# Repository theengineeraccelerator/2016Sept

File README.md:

# 2016Sept
This is for all the design documentation from the September iteration of The Engineer Accelerator. 

The folder for each student contains the work they completed during the course. They are marked with the certificate they received at the end of the course. 

- *Professional Practice* indicates they received a Certificate of Completion in Professional Practice
- *Practice and Execution* indicates they received a Certificate of Completion in Professional Practice and Project Execution
- *Independent* indicates that the project was a independent study and not part of the session

for more information see on certifcation see the [Certification](http://www.engineeraccelerator.com/program/#certification) section of [Program](http://www.engineeraccelerator.com/program/) page

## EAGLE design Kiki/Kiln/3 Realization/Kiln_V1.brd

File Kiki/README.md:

# 2016Sept Kiki
This is for all the design documentation for this course

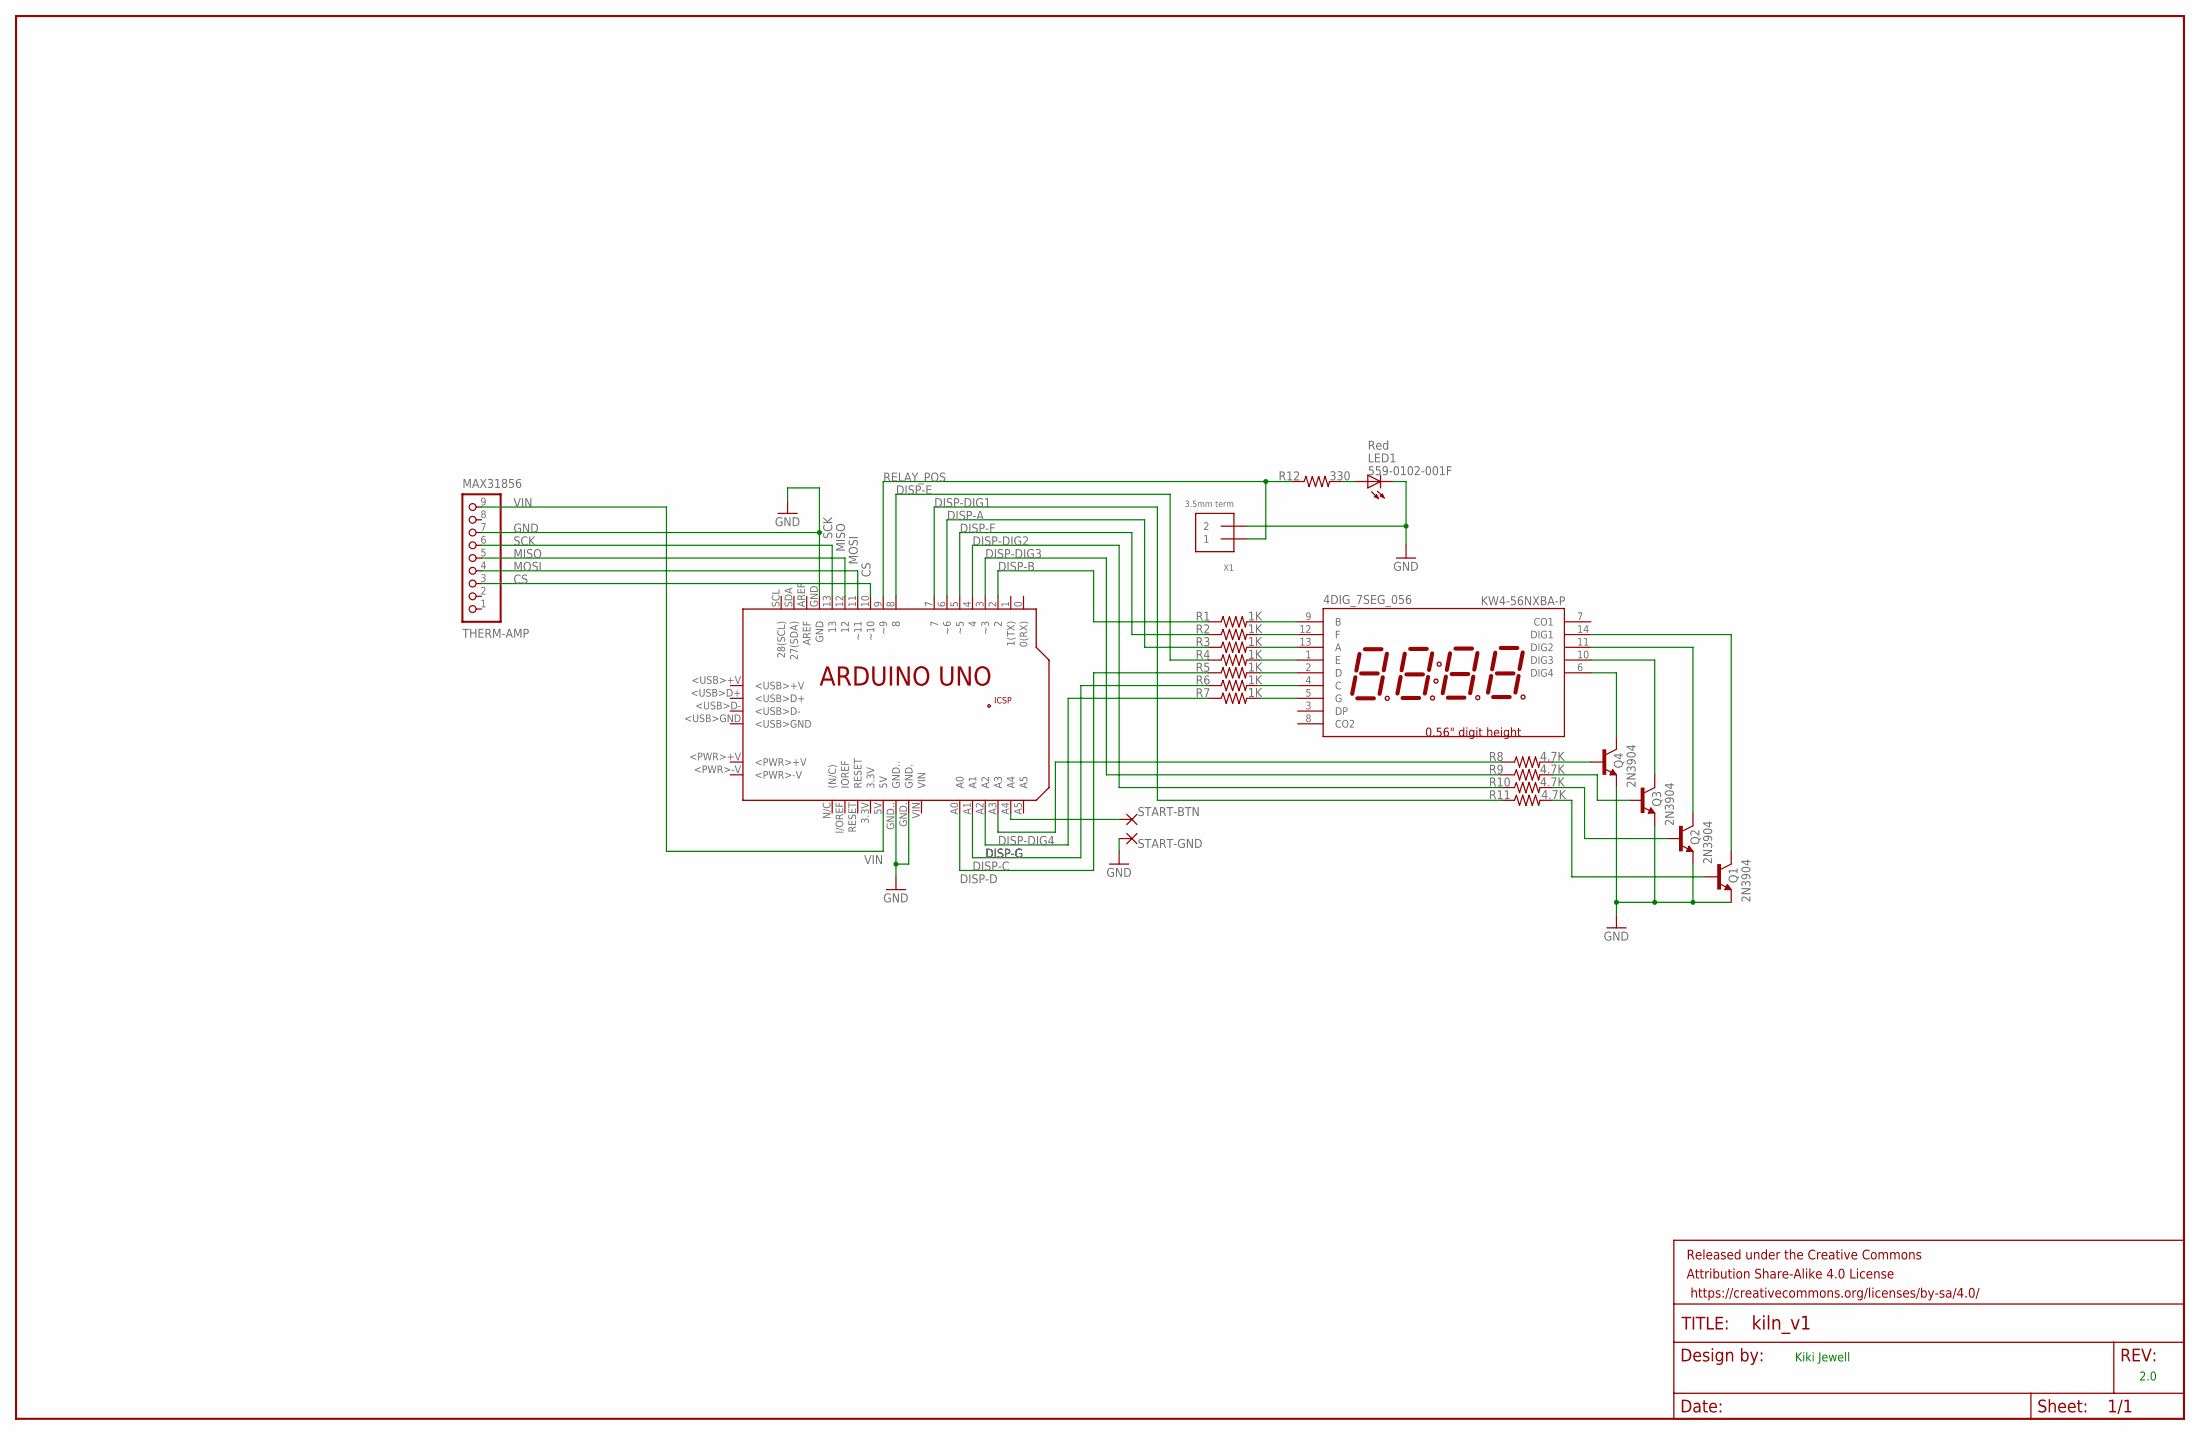
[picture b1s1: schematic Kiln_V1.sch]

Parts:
4DIG_7SEG_056: KW4-56NXBA-P; 4DIG_7SEG_056
FRAME1: FRAME-LEDGER; CREATIVE_COMMONS
LED1: 559-0102-001F; LED3MM
PCB1: ARDUINO_UNO
Q1, Q2, Q3, Q4: 2N3904; TO92
R1, R2, R3, R4, R5, R6, R7: 1K; 1206
R8, R9, R10, R11: 4.7K; 1206
R12: 330; 1206
START-BTN: WIREPAD2,54/1,1; 2,54/1,1
START-GND: WIREPAD2,54/1,1; 2,54/1,1
THERM-AMP: MAX31856; 1X09_ROUND_70
X1: 3.5mm term; TERMBLOCK_1X2-3.5MM

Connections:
A: 4DIG_7SEG_056.13 (A), R3.2
B: 4DIG_7SEG_056.9 (B), R1.2
C: 4DIG_7SEG_056.4 (C), R6.2
CS: PCB1.10 (~10), THERM-AMP.3
D: 4DIG_7SEG_056.2 (D), R5.2
DIG1: 4DIG_7SEG_056.14 (DIG1), Q1.1 (C)
DIG2: 4DIG_7SEG_056.11 (DIG2), Q2.1 (C)
DIG3: 4DIG_7SEG_056.10 (DIG3), Q3.1 (C)
DIG4: 4DIG_7SEG_056.6 (DIG4), Q4.1 (C)
DISP-A: PCB1.6 (~6), R3.1
DISP-B: PCB1.2, R1.1
DISP-C: PCB1.A1, R6.1
DISP-D: PCB1.A0, R5.1
DISP-DIG1: PCB1.7, R11.1
DISP-DIG2: PCB1.4, R10.1
DISP-DIG3: PCB1.3 (~3), R9.1
DISP-DIG4: PCB1.A3, R8.1
DISP-E: PCB1.8, R4.1
DISP-F: PCB1.5 (~5), R2.1
DISP-G: PCB1.A2, R7.1
E: 4DIG_7SEG_056.1 (E), R4.2
F: 4DIG_7SEG_056.12 (F), R2.2
G: 4DIG_7SEG_056.5 (G), R7.2
GND: LED1.K (C), PCB1.GND, PCB1.GND., PCB1.GND.., Q1.3 (E), Q2.3 (E), Q3.3 (E), Q4.3 (E), START-GND.1, THERM-AMP.7, X1.2
MISO: PCB1.12, THERM-AMP.5
MOSI: PCB1.11 (~11), THERM-AMP.4
R8: Q4.2 (B), R8.2
R9: Q3.2 (B), R9.2
R10: Q2.2 (B), R10.2
R11: Q1.2 (B), R11.2
R12: LED1.A, R12.2
RELAY_POS: PCB1.9 (~9), R12.1, X1.1
SCK: PCB1.13, THERM-AMP.6
START-NET: PCB1.A4, START-BTN.1
VIN: PCB1.5V, THERM-AMP.9

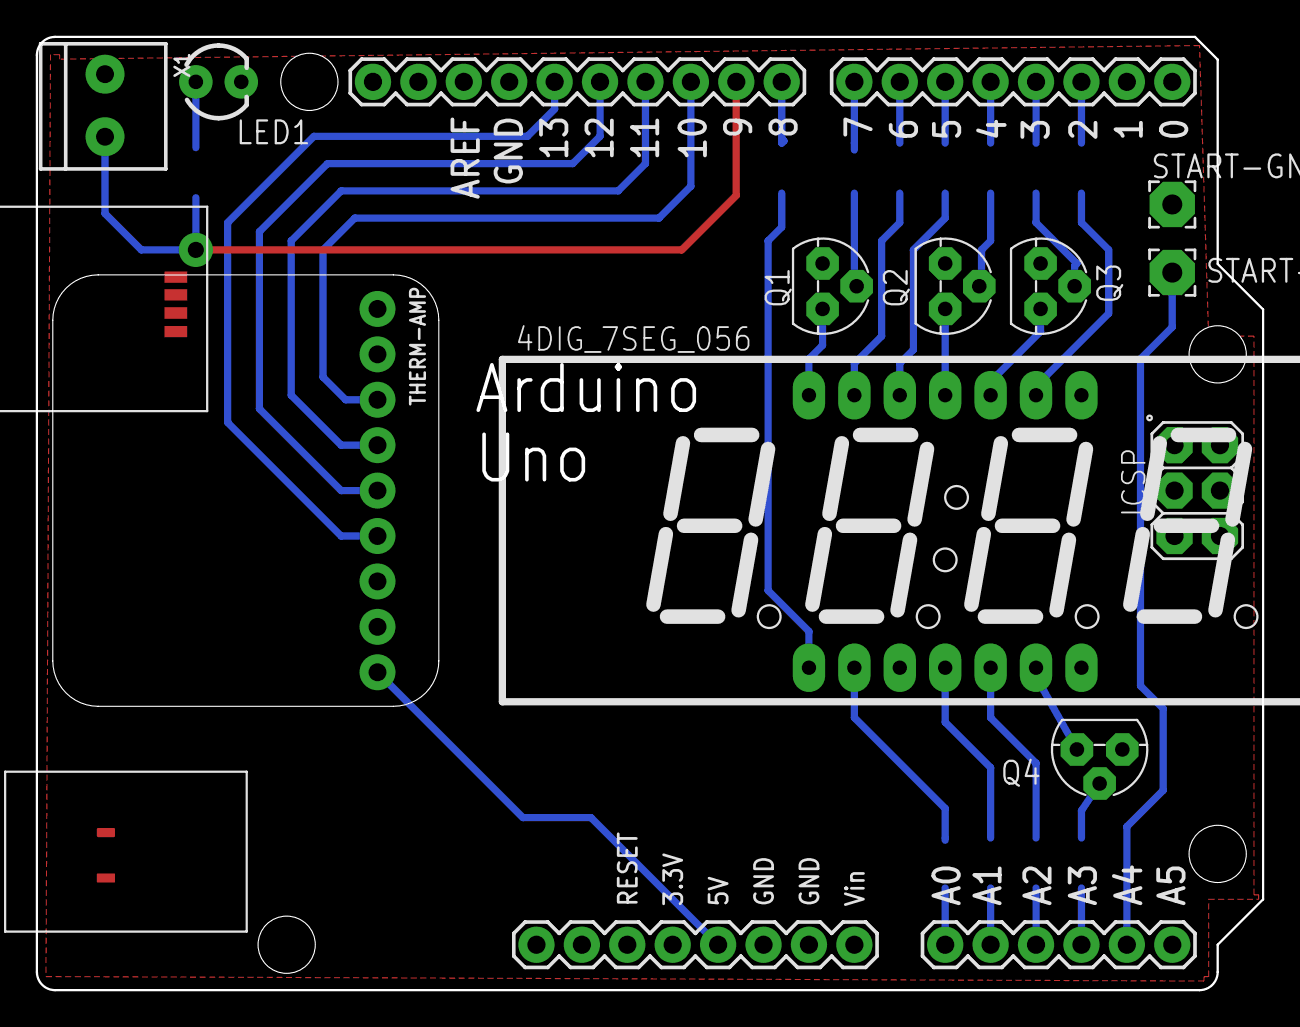
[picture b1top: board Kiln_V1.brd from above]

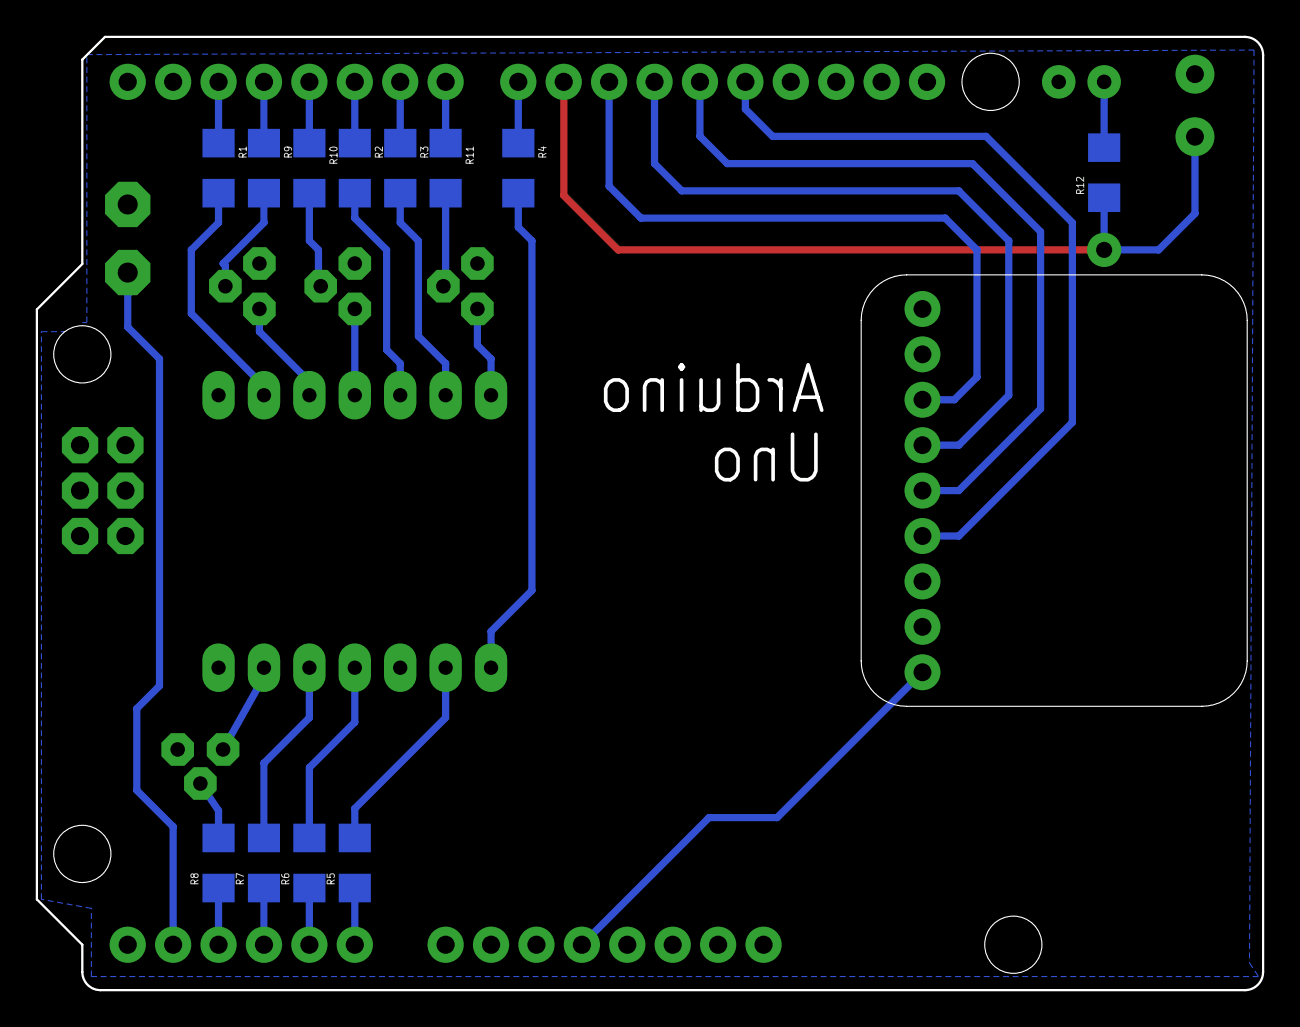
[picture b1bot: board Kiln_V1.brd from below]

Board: 2 copper layers, 68.6 x 53.3 mm, 24 parts (12 on the bottom side), 35 nets.

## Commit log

2016-09-17 Added Student folders
    Store all the work for this class in these folders. Use Github in any
    way you want.
2016-09-17 added test line to README.md
2016-09-17 Added Deliverables and Hours Tracking Templates
2016-09-22 Added Product Definition
2016-09-22 Product Def and Feature block diagram
2016-09-22 adding Electronic Load Block Diagram
2016-09-22 Try again
2016-09-22 Create: Product Definition and Hours Tracking Product Definition: this is the start of the Kiln Product Definition. Detailed Feature list and detailed Behavior definition still left. Also Interface l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
    Hours tracking: made one entry for my estimate for the PD.
    Will update with my hours when done.
2016-09-22 Presentation PDFs for the 1st week
    These are PDF of the slides we when over the first week that you can
    use as a reference
2016-09-22 Review of first release of the Product Definition
2016-09-24 Adding: Acceptance Criteria Getting started on this, but not done. Holding off to start other parts so I'm sure I know how to complete them on my own.
2016-09-24 Add: more Deliverables I added all the deliverables from my notes so far. Won't touch this file again. :)
2016-09-26 Upload major component bomb
2016-09-26 Updated Deliverables
    For Hours Tracking, Architecture and Realization
2016-09-27 Added BOM: All parts added All parts are added and priced. Going to do a quick search for cheaper, and re-push in a half hour.
2016-09-27 Updated BOM: found cheaper, better parts Cheaper LED display from Jameco. And pretty neon indicators, which needed triacs, added. Pretty much same cost.
2016-09-28 Hardware block diagram/Architecture
2016-10-01 Updated Deliverables Tracking
2016-10-03 Update: Product Architecture (pinouts) Starting on the pinouts. Close to done.
2016-10-04 Added: Eagle files (Kiln_V1) Added the .brd, .lbr, .sch files for the Kiln. I've gotten the first pass on traces done, but there are a couple issues. First, the transitors aren't grounded (yet). Seco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
2016-10-04 Updated: 3.3v & GND Disconnected the 3.3v pin -- the was a supply pin, not a power in pin. Attached the GND for the transistors to BOTH Arduino ground pins, and beefec up the trace, just in case. I w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
2016-10-04 Update: minor changes Changed the name of the Thermal Amplifier JP3 connector, for clarity.
2016-10-05 Updated Deliverables Tracking and Added Presentation slides
2016-10-06 Update: new display The display file was the wrong size. Rebuilt it. Layout got horked, so had to rebuild it from scratch. Also added the relay and Heating indicator light.
2016-10-06 Update: changed R12, LED Replaced these with real parts. Cleared the ERC. But this does not follow proper guidelines.
2016-10-06 Update: cleared DRC errors Have not fixed the Drill errors, but cleared the main ones.
2016-10-06 Update: DRC errors cleared All the drill errors are clear now. Some vias were eliminated. (Still need to consolidate drill sizes I think.)
2016-10-07 preliminary review of the schematic and layout
2016-10-10 Pushing product arch
    Updated schematic
2016-10-11 Add/Update: to level 3 Realization Added Feature_Block_Diagram, Hardware Block DIagram, Product Architecture Made all the changes in the Deliverable Review.
2016-10-11 Update: nets are named I had used Wire instead of Net, so I had to rework everything. But it's done. All nets are named.
2016-10-11 Added Gerbers
    REV_01_gerbers added
2016-10-11 review of kiln schematic and layout
2016-10-11 Added top and bottom layout picture for the DDS and update deliverable review
2016-10-12 review Architecture and PD
2016-10-12 reviewed Arduino DDS architecture
2016-10-12 Added: start button Added pads for soldering the Start Button. Also added the 7seg4dig library, which seems wasn't added. Note: Copy to Library was grayed out.
2016-10-13 rearranging of folders, addons to files
2016-10-13 Added portfolios folders to student folders
2016-10-13 Adding images of diagrams and scrap notes for later
2016-10-13 Update: Comments addressed Product Definition has been edited to reflect the Review document.
2016-10-13 Added project scoping example and template
2016-10-13 Update: final comments Fixed all the things listed in the final comments
2016-10-13 Update: comments on what I fixed I added detailed comments on what fixes I made.
2016-10-13 Update: reworked, clearer I gave in and reworked the entire document. The flow of information works a whole lot better, flowing from left to right. The Start Button flows to the Arduino, which flows 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
2016-10-14 Electronic Load Review
2016-10-14 Kiln Controller Review
2016-10-14 voltage divider resistance value for cv, removed divider going to dac
2016-10-14 Eagle files and pdf of schematic
2016-10-14 Sheet bringup
    Prepare for ultimate submit
2016-10-14 Fabrication output
    updated PCB board/schematic + output library
2016-10-14 gitignore and redraw of diagrams based on feedback
2016-10-14 Presentation update
    Presention update
2016-10-14 To be done list
    Added timeline
2016-10-14 commit
    LaptopLocal stuff
2016-10-15 Added deliverables to Portfolio folder
2016-10-15 Final Release
    Release
2016-10-17 Uploaded last presentations
2017-01-26 removed old presentations
2017-02-22 Updated folder names
    so they reflect certification level

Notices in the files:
parts and their libraries:
microbuilder: This work is placed in the public domain, and may be freely used for commercial and non-commercial work with the following conditions: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
Kiln_V2_0.0: Released under the Creative Commons Attribution Share-Alike 4.0 License
Kiln_V2_0.0: https://creativecommons.org/licenses/by-sa/4.0
